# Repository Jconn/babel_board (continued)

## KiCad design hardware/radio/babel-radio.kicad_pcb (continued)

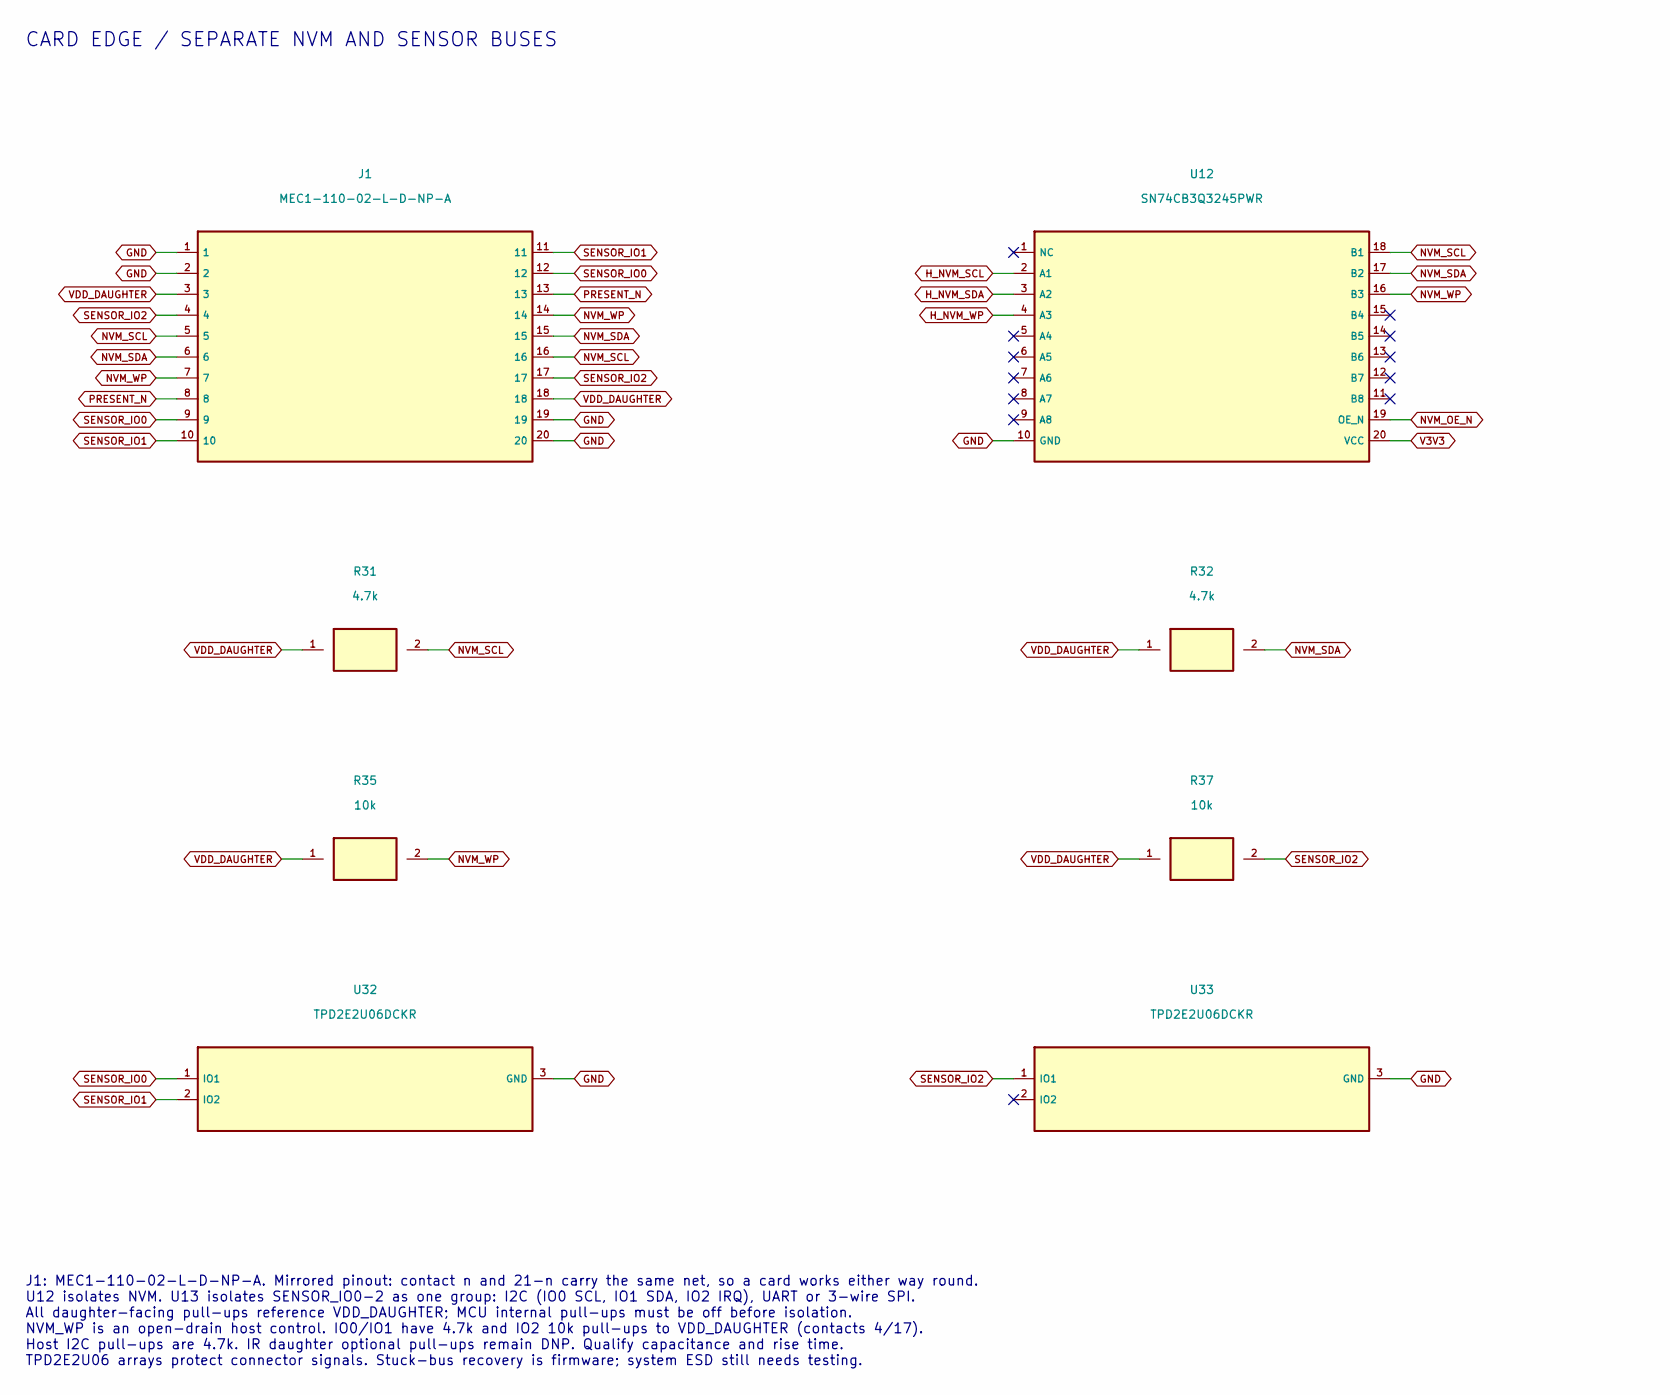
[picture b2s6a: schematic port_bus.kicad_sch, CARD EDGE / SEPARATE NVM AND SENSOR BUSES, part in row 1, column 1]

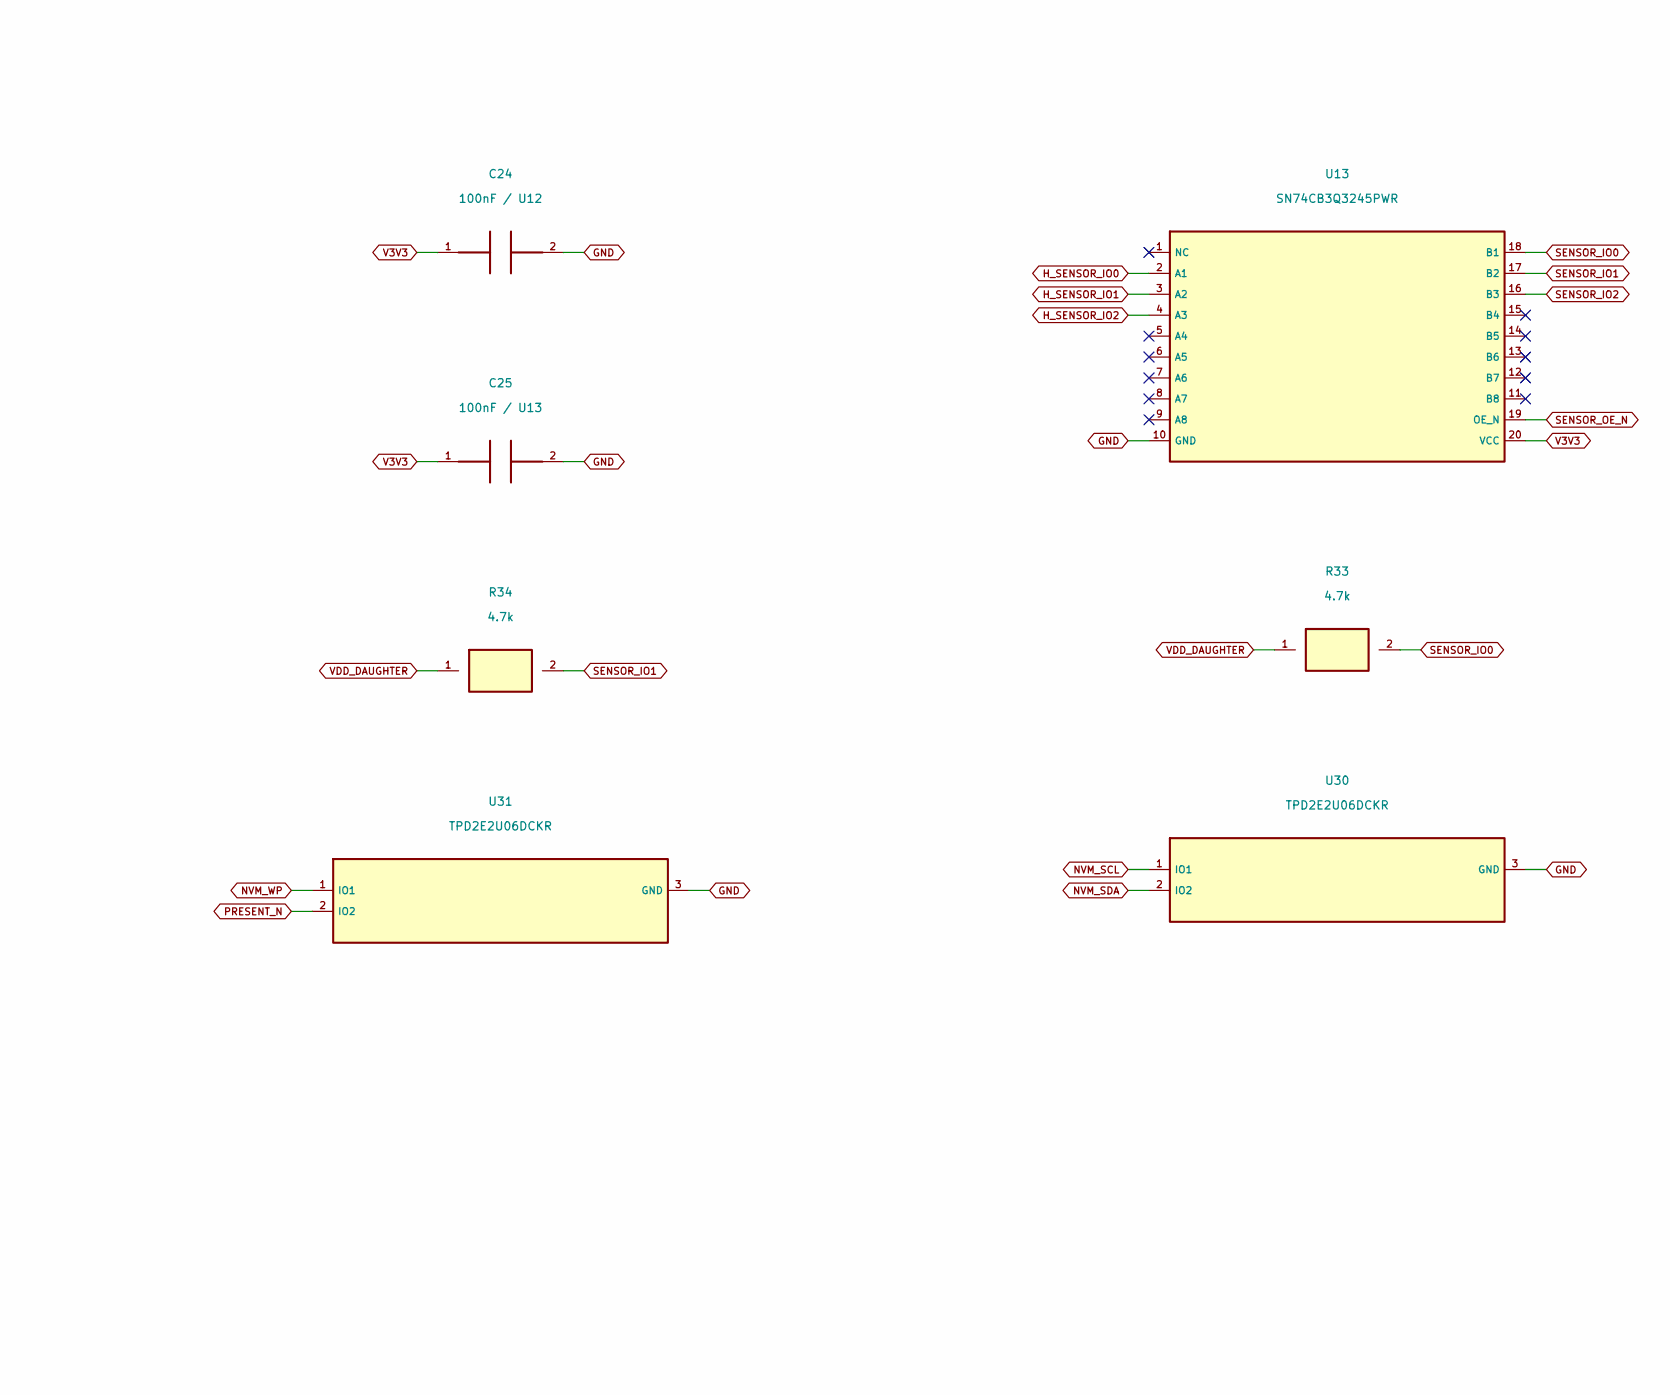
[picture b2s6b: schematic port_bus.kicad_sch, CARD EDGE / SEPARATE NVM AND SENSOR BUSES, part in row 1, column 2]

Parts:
C24: 100nF / U12; C_0805_2012Metric
C25: 100nF / U13; C_0805_2012Metric
J1: MEC1-110-02-L-D-NP-A; MEC1_110_02_NP_A_Socket
R31, R32, R33, R34: 4.7k; R_0603_1608Metric
R35, R37: 10k; R_0603_1608Metric
U12, U13: SN74CB3Q3245PWR; TSSOP-20_4.4x6.5mm_P0.65mm
U30, U31, U32, U33: TPD2E2U06DCKR; SOT-323_SC-70

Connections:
GND: C24.2, C25.2, J1.1, J1.2, J1.19, J1.20, U12.10 (GND), U13.10 (GND), U30.3 (GND), U31.3 (GND), U32.3 (GND), U33.3 (GND); also elsewhere on the board
H_NVM_SCL: U12.2 (A1); also elsewhere on the board
H_NVM_SDA: U12.3 (A2); also elsewhere on the board
H_NVM_WP: U12.4 (A3); also elsewhere on the board
H_SENSOR_IO0: U13.2 (A1); also elsewhere on the board
H_SENSOR_IO1: U13.3 (A2); also elsewhere on the board
H_SENSOR_IO2: U13.4 (A3); also elsewhere on the board
NVM_OE_N: U12.19 (OE_N); also elsewhere on the board
NVM_SCL: J1.5, J1.16, R31.2, U12.18 (B1), U30.1 (IO1)
NVM_SDA: J1.6, J1.15, R32.2, U12.17 (B2), U30.2 (IO2)
NVM_WP: J1.7, J1.14, R35.2, U12.16 (B3), U31.1 (IO1)
PRESENT_N: J1.8, J1.13, U31.2 (IO2); also elsewhere on the board
SENSOR_IO0: J1.9, J1.12, R33.2, U13.18 (B1), U32.1 (IO1)
SENSOR_IO1: J1.10, J1.11, R34.2, U13.17 (B2), U32.2 (IO2)
SENSOR_IO2: J1.4, J1.17, R37.2, U13.16 (B3), U33.1 (IO1)
SENSOR_OE_N: U13.19 (OE_N); also elsewhere on the board
V3V3: C24.1, C25.1, U12.20 (VCC), U13.20 (VCC); also elsewhere on the board
VDD_DAUGHTER: J1.3, J1.18, R31.1, R32.1, R33.1, R34.1, R35.1, R37.1; also elsewhere on the board

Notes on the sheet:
CARD EDGE / SEPARATE NVM AND SENSOR BUSES
J1: MEC1-110-02-L-D-NP-A. Mirrored pinout: contact n and 21-n carry the same net, so a card works either way round. U12 isolates NVM. U13 isolates SENSOR_IO0-2 as one group: I2C (IO0 SCL, IO1 SDA, IO2 IRQ), UART or 3-wire SPI. All daughter-facing pull-ups reference VDD_DAUGHTER; MCU internal pull-u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

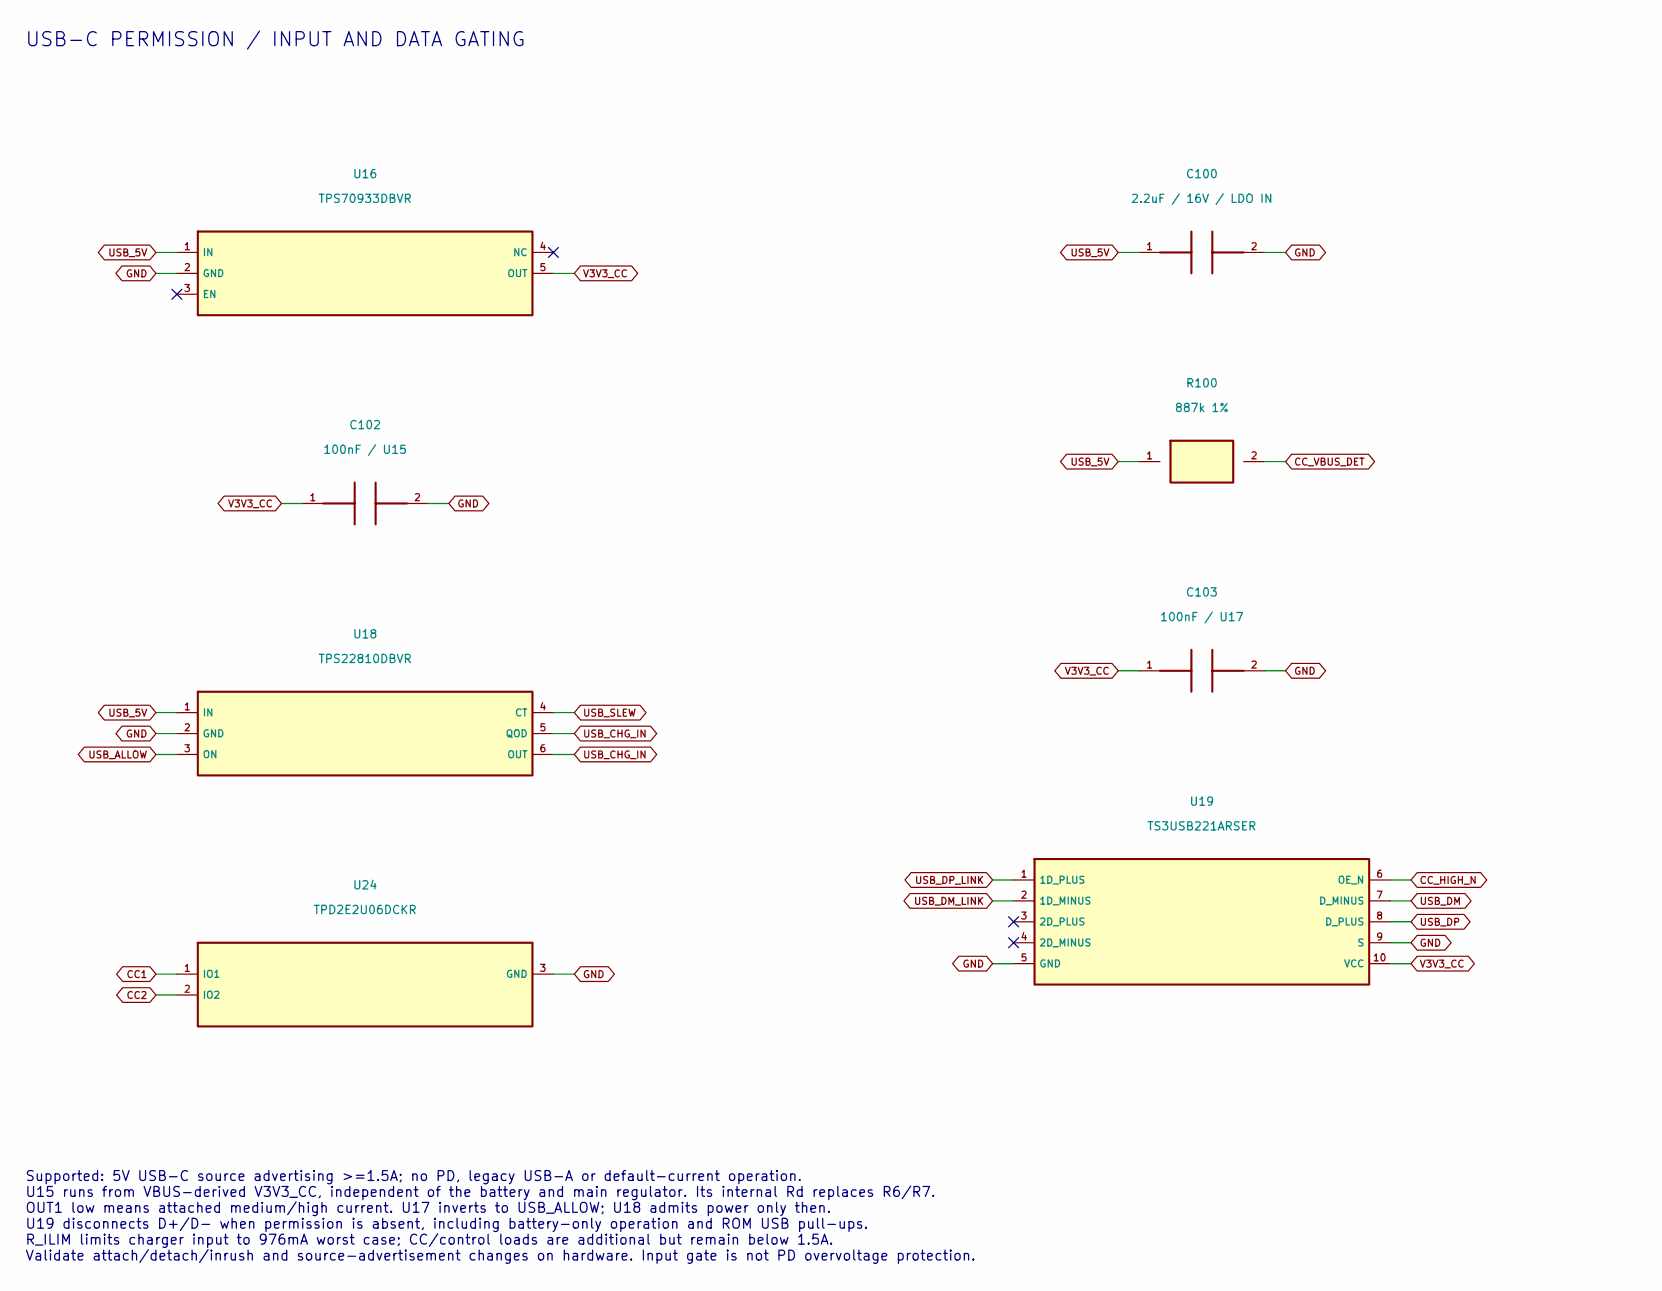
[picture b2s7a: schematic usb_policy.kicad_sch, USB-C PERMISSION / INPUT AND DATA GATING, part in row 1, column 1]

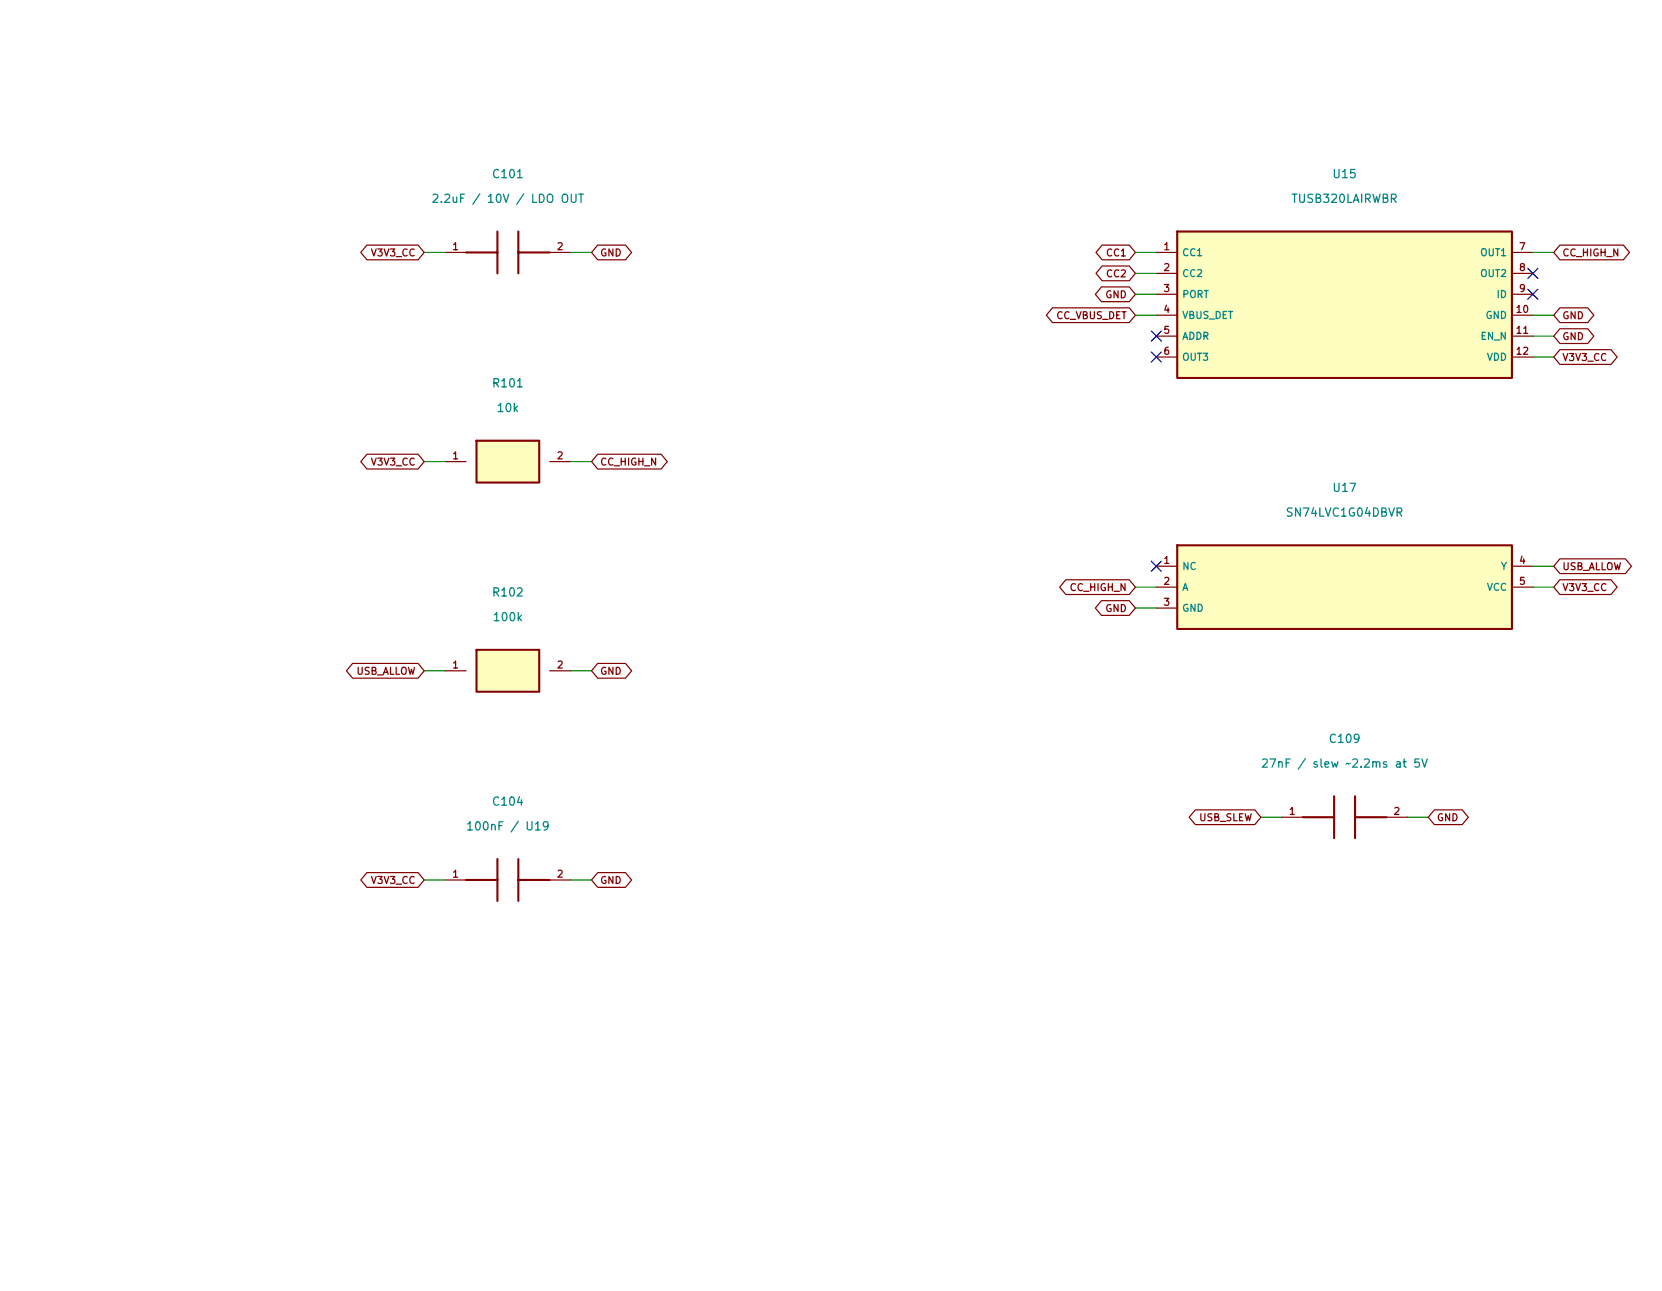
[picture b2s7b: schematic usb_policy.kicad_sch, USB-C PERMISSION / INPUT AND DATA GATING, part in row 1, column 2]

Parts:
C100: 2.2uF / 16V / LDO IN; C_0805_2012Metric
C101: 2.2uF / 10V / LDO OUT; C_0805_2012Metric
C102: 100nF / U15; C_0805_2012Metric
C103: 100nF / U17; C_0805_2012Metric
C104: 100nF / U19; C_0805_2012Metric
C109: 27nF / slew ~2.2ms at 5V; C_0805_2012Metric
R100: 887k 1%; R_0603_1608Metric
R101: 10k; R_0603_1608Metric
R102: 100k; R_0603_1608Metric
U15: TUSB320LAIRWBR; Texas_X2QFN-12_1.6x1.6mm_P0.4mm
U16: TPS70933DBVR; SOT-23-5
U17: SN74LVC1G04DBVR; SOT-23-5
U18: TPS22810DBVR; SOT-23-6
U19: TS3USB221ARSER; Texas_UQFN-10_1.5x2mm_P0.5mm
U24: TPD2E2U06DCKR; SOT-323_SC-70

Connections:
CC1: U15.1 (CC1), U24.1 (IO1); also elsewhere on the board
CC2: U15.2 (CC2), U24.2 (IO2); also elsewhere on the board
CC_HIGH_N: R101.2, U15.7 (OUT1), U17.2 (A), U19.6 (OE_N); also elsewhere on the board
CC_VBUS_DET: R100.2, U15.4 (VBUS_DET)
GND: C100.2, C101.2, C102.2, C103.2, C104.2, C109.2, R102.2, U15.3 (PORT), U15.10 (GND), U15.11 (EN_N), U16.2 (GND), U17.3 (GND), U18.2 (GND), U19.5 (GND), U19.9 (S), U24.3 (GND); also elsewhere on the board
USB_5V: C100.1, R100.1, U16.1 (IN), U18.1 (IN); also elsewhere on the board
USB_ALLOW: R102.1, U17.4 (Y), U18.3 (ON); also elsewhere on the board
USB_CHG_IN: U18.5 (QOD), U18.6 (OUT); also elsewhere on the board
USB_DM: U19.7 (D_MINUS); also elsewhere on the board
USB_DM_LINK: U19.2 (1D_MINUS); also elsewhere on the board
USB_DP: U19.8 (D_PLUS); also elsewhere on the board
USB_DP_LINK: U19.1 (1D_PLUS); also elsewhere on the board
USB_SLEW: C109.1, U18.4 (CT)
V3V3_CC: C101.1, C102.1, C103.1, C104.1, R101.1, U15.12 (VDD), U16.5 (OUT), U17.5 (VCC), U19.10 (VCC); also elsewhere on the board

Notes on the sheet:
USB-C PERMISSION / INPUT AND DATA GATING
Supported: 5V USB-C source advertising >=1.5A; no PD, legacy USB-A or default-current operation. U15 runs from VBUS-derived V3V3_CC, independent of the battery and main regulator. Its internal Rd replaces R6/R7. OUT1 low means attached medium/high current. U17 inverts to USB_ALLOW; U18 admits power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

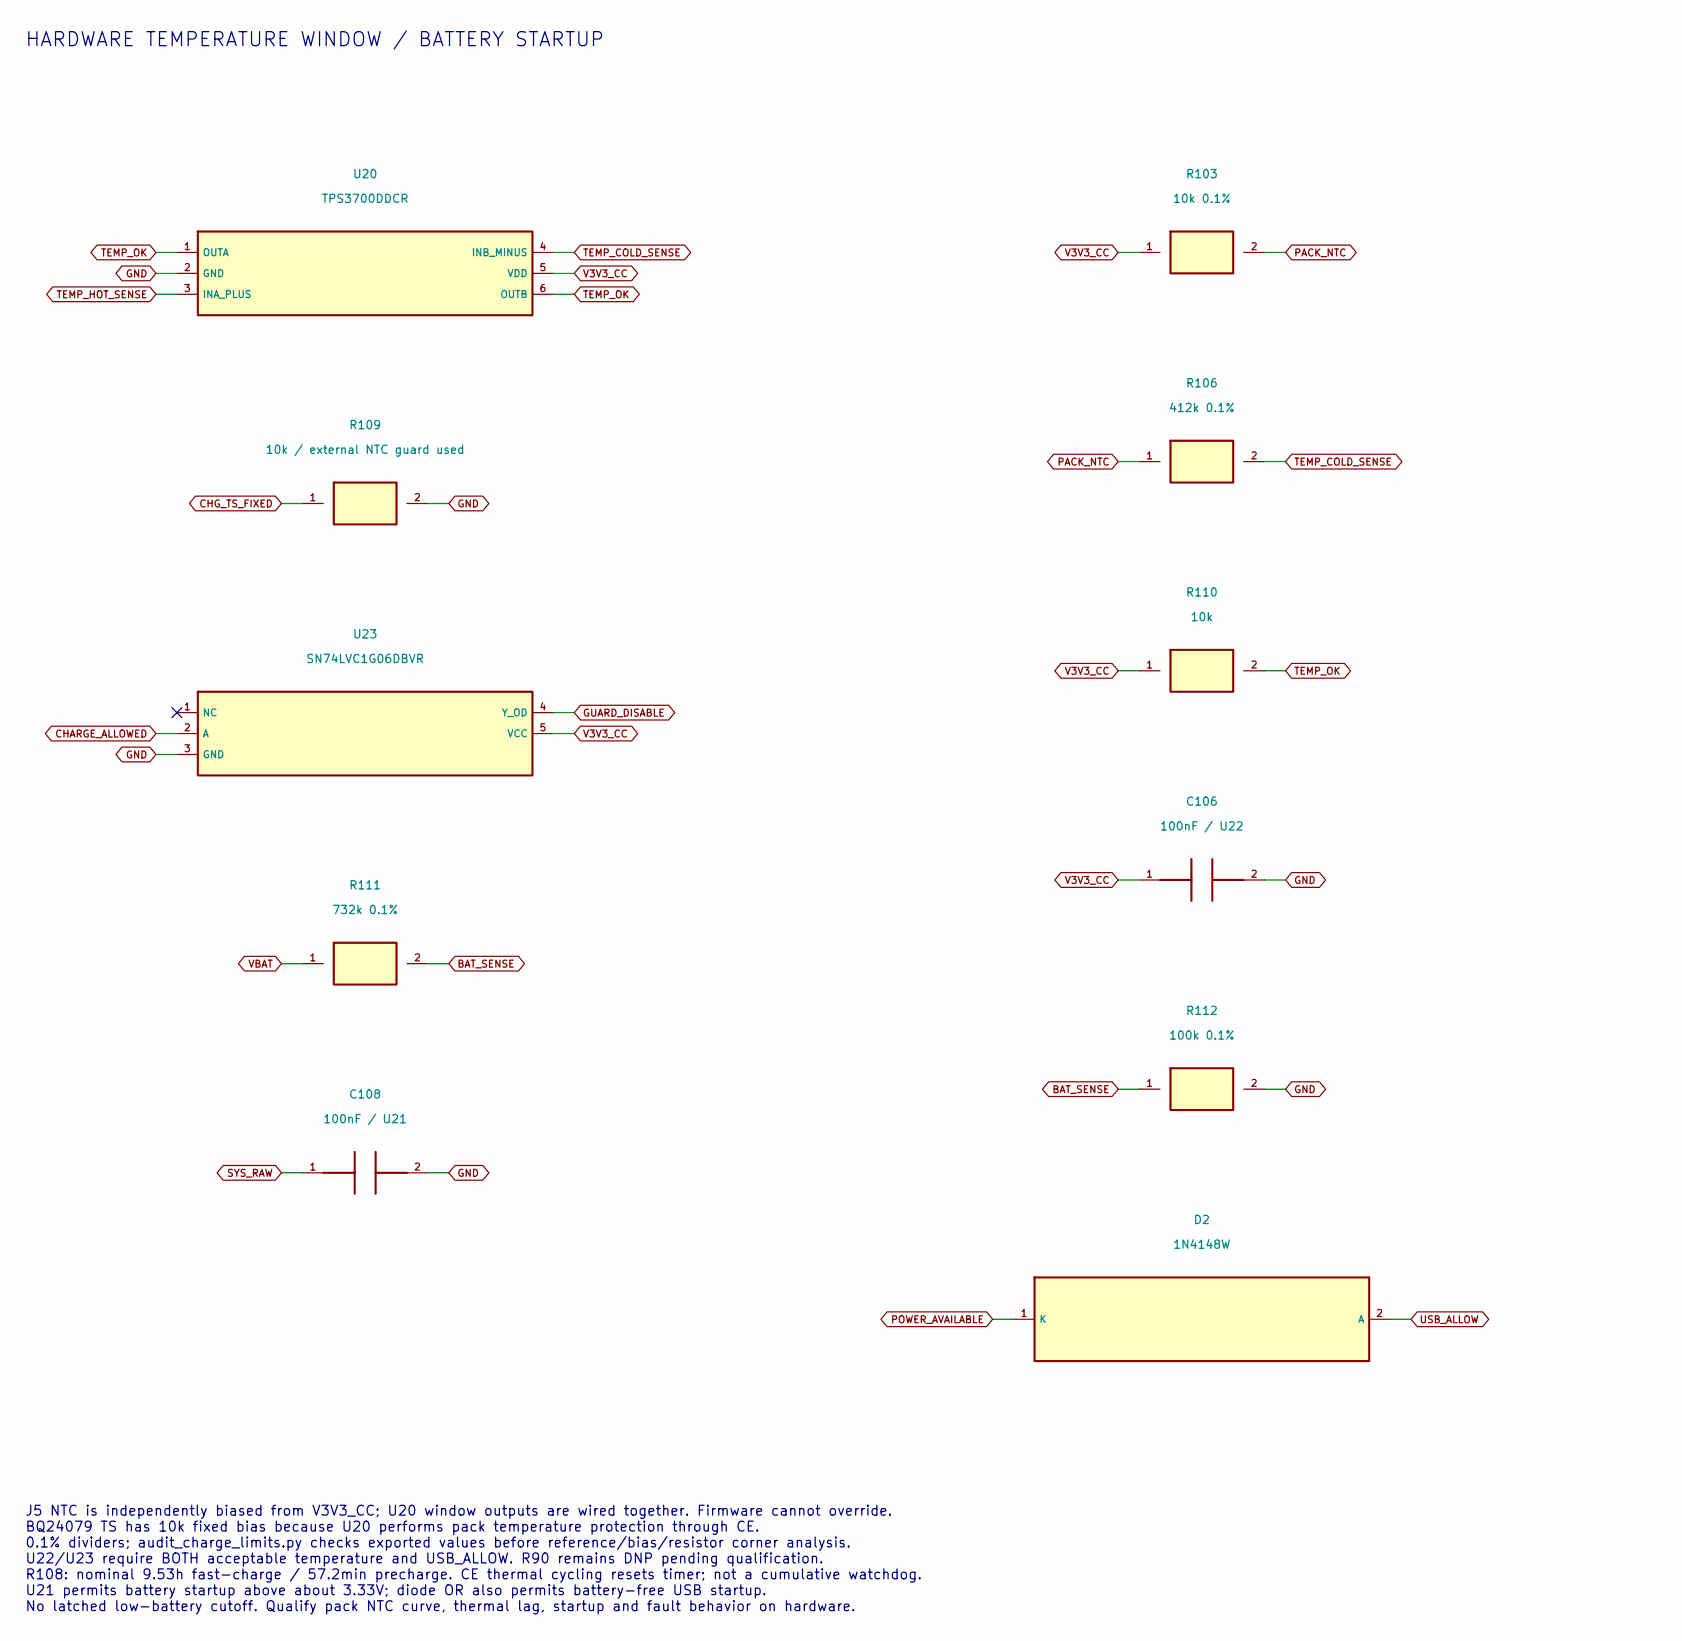
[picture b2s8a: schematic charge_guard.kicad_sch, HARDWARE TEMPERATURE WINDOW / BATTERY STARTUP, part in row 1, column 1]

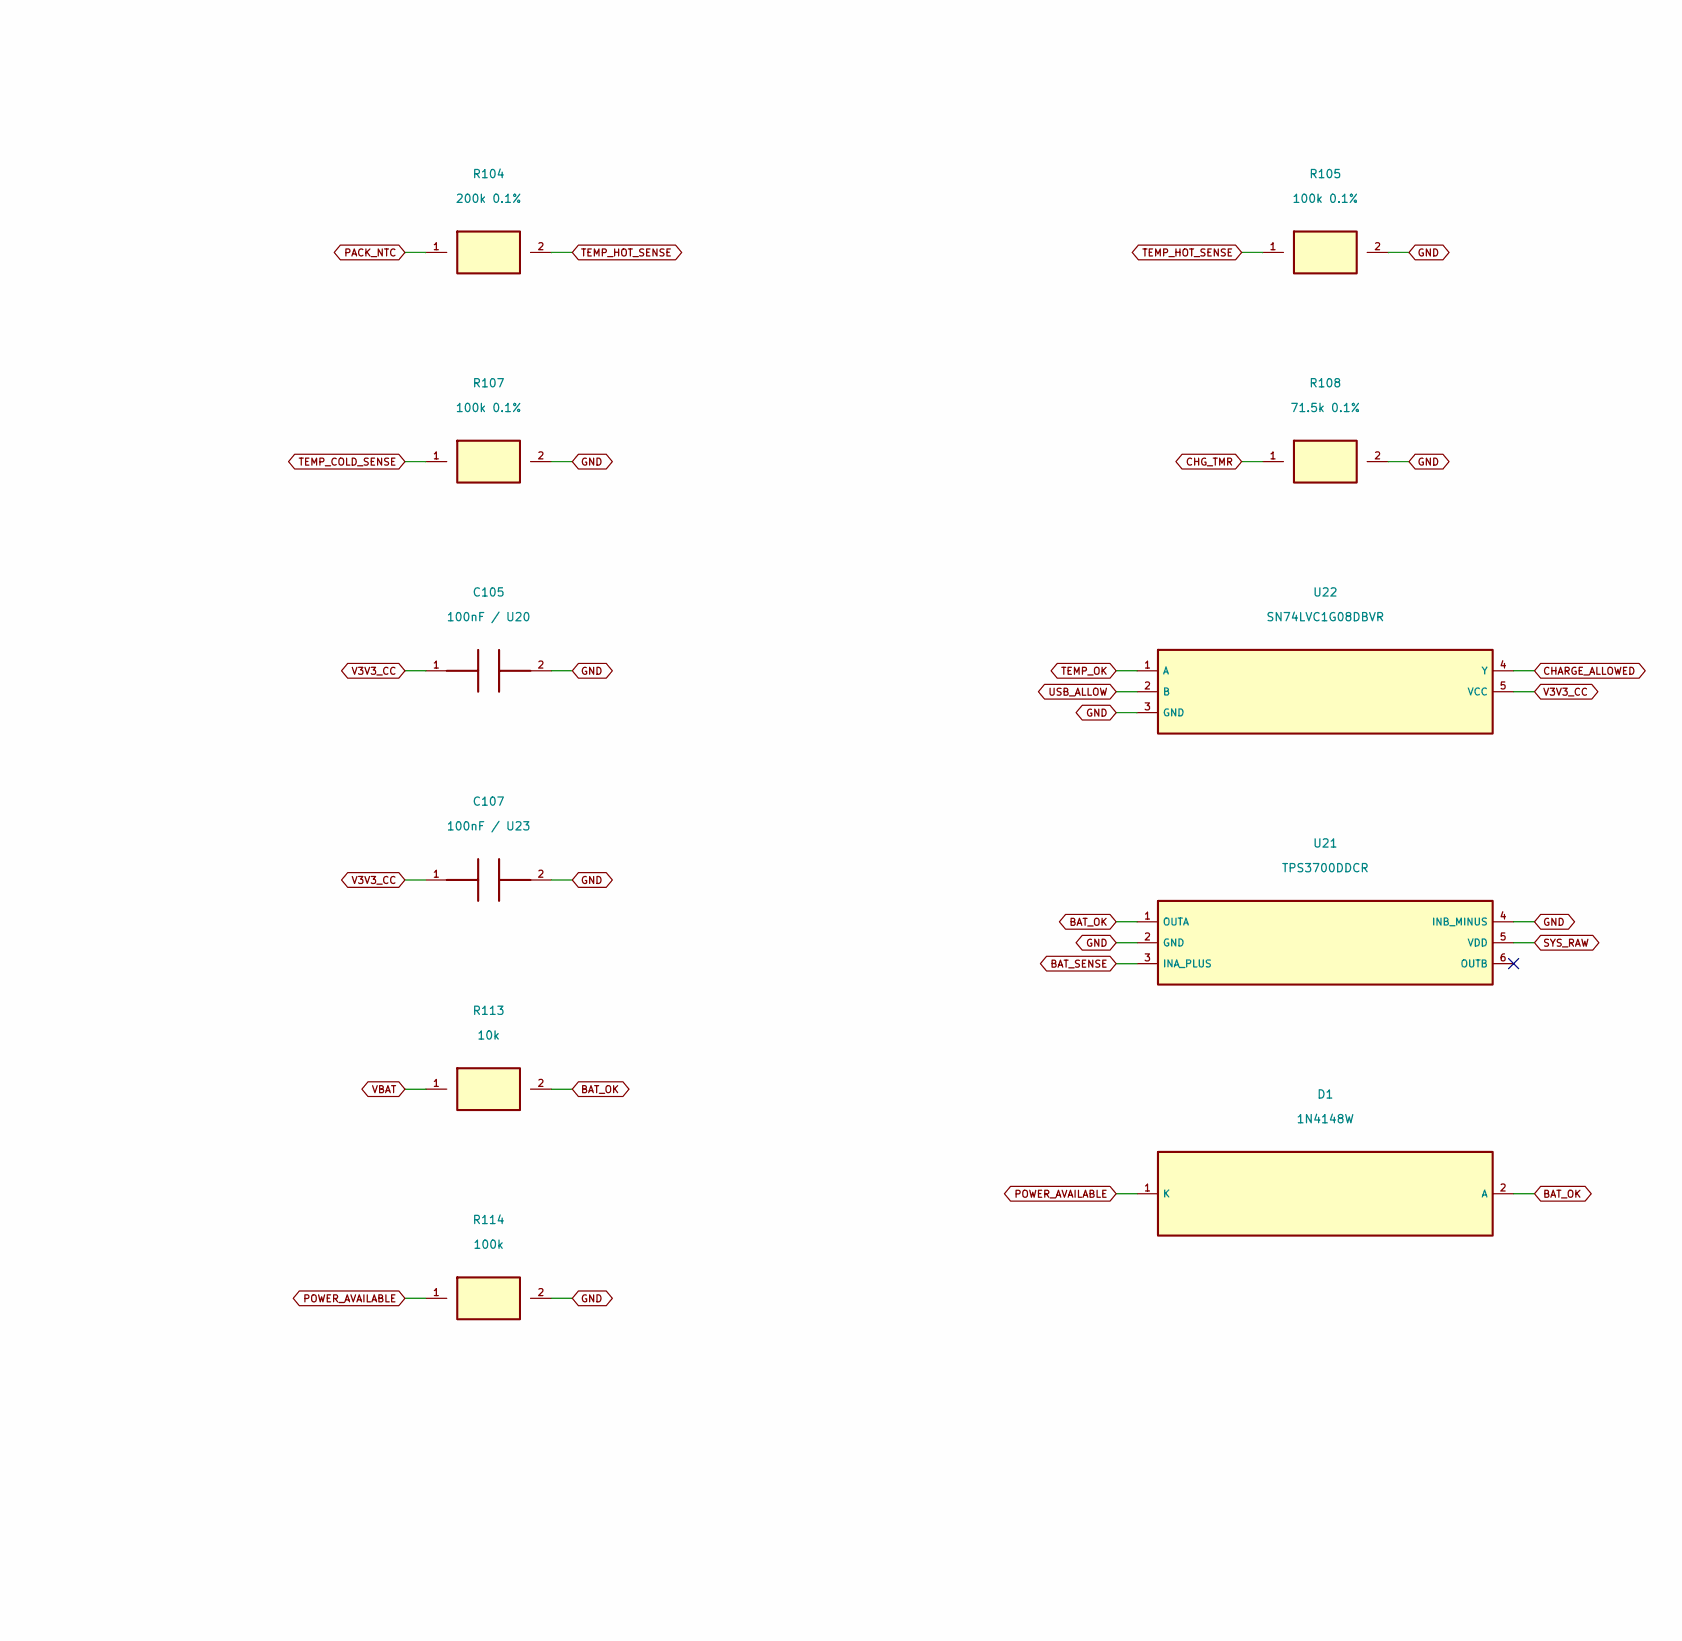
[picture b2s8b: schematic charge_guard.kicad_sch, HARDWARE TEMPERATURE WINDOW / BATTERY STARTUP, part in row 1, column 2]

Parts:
C105: 100nF / U20; C_0805_2012Metric
C106: 100nF / U22; C_0805_2012Metric
C107: 100nF / U23; C_0805_2012Metric
C108: 100nF / U21; C_0805_2012Metric
D1, D2: 1N4148W; D_SOD-123
R103: 10k 0.1%; R_0603_1608Metric
R104: 200k 0.1%; R_0603_1608Metric
R105, R107, R112: 100k 0.1%; R_0603_1608Metric
R106: 412k 0.1%; R_0603_1608Metric
R108: 71.5k 0.1%; R_0603_1608Metric
R109: 10k / external NTC guard used; R_0603_1608Metric
R110, R113: 10k; R_0603_1608Metric
R111: 732k 0.1%; R_0603_1608Metric
R114: 100k; R_0603_1608Metric
U20, U21: TPS3700DDCR; SOT-23-6
U22: SN74LVC1G08DBVR; SOT-23-5
U23: SN74LVC1G06DBVR; SOT-23-5

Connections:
BAT_OK: D1.2 (A), R113.2, U21.1 (OUTA); also elsewhere on the board
BAT_SENSE: R111.2, R112.1, U21.3 (INA_PLUS)
CHARGE_ALLOWED: U22.4 (Y), U23.2 (A)
CHG_TMR: R108.1; also elsewhere on the board
CHG_TS_FIXED: R109.1; also elsewhere on the board
GND: C105.2, C106.2, C107.2, C108.2, R105.2, R107.2, R108.2, R109.2, R112.2, R114.2, U20.2 (GND), U21.2 (GND), U21.4 (INB_MINUS), U22.3 (GND), U23.3 (GND); also elsewhere on the board
GUARD_DISABLE: U23.4 (Y_OD); also elsewhere on the board
PACK_NTC: R103.2, R104.1, R106.1; also elsewhere on the board
POWER_AVAILABLE: D1.1 (K), D2.1 (K), R114.1; also elsewhere on the board
SYS_RAW: C108.1, U21.5 (VDD); also elsewhere on the board
TEMP_COLD_SENSE: R106.2, R107.1, U20.4 (INB_MINUS)
TEMP_HOT_SENSE: R104.2, R105.1, U20.3 (INA_PLUS)
TEMP_OK: R110.2, U20.1 (OUTA), U20.6 (OUTB), U22.1 (A); also elsewhere on the board
USB_ALLOW: D2.2 (A), U22.2 (B); also elsewhere on the board
V3V3_CC: C105.1, C106.1, C107.1, R103.1, R110.1, U20.5 (VDD), U22.5 (VCC), U23.5 (VCC); also elsewhere on the board
VBAT: R111.1, R113.1; also elsewhere on the board

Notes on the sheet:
HARDWARE TEMPERATURE WINDOW / BATTERY STARTUP
J5 NTC is independently biased from V3V3_CC; U20 window outputs are wired together. Firmware cannot override. BQ24079 TS has 10k fixed bias because U20 performs pack temperature protection through CE. 0.1% dividers; audit_charge_limits.py checks exported values before reference/bias/resistor corner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

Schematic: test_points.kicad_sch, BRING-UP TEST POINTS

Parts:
TP1, TP7: GND; TestPoint_Pad_D1.0mm
TP2: USB_5V; TestPoint_Pad_D1.0mm
TP3: USB_CHG_IN; TestPoint_Pad_D1.0mm
TP4: VBAT; TestPoint_Pad_D1.0mm
TP5: SYS_RAW; TestPoint_Pad_D1.0mm
TP6: CHG_N; TestPoint_Pad_D1.0mm
TP8: V3V3; TestPoint_Pad_D1.0mm
TP9: REG_EN; TestPoint_Pad_D1.0mm
TP10: REG_PG; TestPoint_Pad_D1.0mm
TP11: PACK_NTC; TestPoint_Pad_D1.0mm
TP12: TEMP_OK; TestPoint_Pad_D1.0mm
TP13: CHARGE_DISABLE; TestPoint_Pad_D1.0mm
TP14: VDD_DAUGHTER; TestPoint_Pad_D1.0mm
TP15: PORT_EN; TestPoint_Pad_D1.0mm
TP16: USB_ALLOW; TestPoint_Pad_D1.0mm

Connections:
CHARGE_DISABLE: TP13.1; also elsewhere on the board
CHG_N: TP6.1; also elsewhere on the board
GND: TP1.1, TP7.1; also elsewhere on the board
PACK_NTC: TP11.1; also elsewhere on the board
PORT_EN: TP15.1; also elsewhere on the board
REG_EN: TP9.1; also elsewhere on the board
REG_PG: TP10.1; also elsewhere on the board
SYS_RAW: TP5.1; also elsewhere on the board
TEMP_OK: TP12.1; also elsewhere on the board
USB_5V: TP2.1; also elsewhere on the board
USB_ALLOW: TP16.1; also elsewhere on the board
USB_CHG_IN: TP3.1; also elsewhere on the board
V3V3: TP8.1; also elsewhere on the board
VBAT: TP4.1; also elsewhere on the board
VDD_DAUGHTER: TP14.1; also elsewhere on the board

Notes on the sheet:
BRING-UP TEST POINTS
Place supply probes with a nearby ground probe. Keep USB data and RF paths free of probe stubs. PACK_NTC probe: use high impedance only; loading can change temperature thresholds. Charging remains disabled until R90 qualification. No high-current injection through probe pads.

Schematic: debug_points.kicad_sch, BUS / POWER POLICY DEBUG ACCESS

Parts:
TP17: H_NVM_SCL; TestPoint_Pad_D1.0mm
TP18: H_NVM_SDA; TestPoint_Pad_D1.0mm
TP19: H_NVM_WP; TestPoint_Pad_D1.0mm
TP20: H_SENSOR_IO0; TestPoint_Pad_D1.0mm
TP21: H_SENSOR_IO1; TestPoint_Pad_D1.0mm
TP22: NVM_OE_N; TestPoint_Pad_D1.0mm
TP23: SENSOR_OE_N; TestPoint_Pad_D1.0mm
TP24: PORT_FAULT_N; TestPoint_Pad_D1.0mm
TP25: PRESENT_N; TestPoint_Pad_D1.0mm
TP26, TP32, TP33, TP34, TP36, TP37, TP38: GND; TestPoint_Pad_D1.0mm
TP27: V3V3_CC; TestPoint_Pad_D1.0mm
TP28: CC_HIGH_N; TestPoint_Pad_D1.0mm
TP29: USB_PGOOD_N; TestPoint_Pad_D1.0mm
TP30: BAT_OK; TestPoint_Pad_D1.0mm
TP31: POWER_AVAILABLE; TestPoint_Pad_D1.0mm
TP35: V3V3_REG; TestPoint_Pad_D1.0mm

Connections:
BAT_OK: TP30.1; also elsewhere on the board
CC_HIGH_N: TP28.1; also elsewhere on the board
GND: TP26.1, TP32.1, TP33.1, TP34.1, TP36.1, TP37.1, TP38.1; also elsewhere on the board
H_NVM_SCL: TP17.1; also elsewhere on the board
H_NVM_SDA: TP18.1; also elsewhere on the board
H_NVM_WP: TP19.1; also elsewhere on the board
H_SENSOR_IO0: TP20.1; also elsewhere on the board
H_SENSOR_IO1: TP21.1; also elsewhere on the board
NVM_OE_N: TP22.1; also elsewhere on the board
PORT_FAULT_N: TP24.1; also elsewhere on the board
POWER_AVAILABLE: TP31.1; also elsewhere on the board
PRESENT_N: TP25.1; also elsewhere on the board
SENSOR_OE_N: TP23.1; also elsewhere on the board
USB_PGOOD_N: TP29.1; also elsewhere on the board
V3V3_CC: TP27.1; also elsewhere on the board
V3V3_REG: TP35.1; also elsewhere on the board

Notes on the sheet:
BUS / POWER POLICY DEBUG ACCESS
1 mm exposed pads: solder fine wires for logic analysis; no permanent headers required. Host I2C is upstream of isolation; daughter test pads expose downstream I2C and WP. Observe control signals, do not force them against outputs. Ground pads support local probes. No added USB-data, CC-pin, switch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
